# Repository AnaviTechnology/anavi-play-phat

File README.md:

# Anavi Play pHAT

Anavi Play pHAT is a simple open source hardware keyboard for Raspberry Pi pHAT (add-on board). Furthermore it supports reading data from various I2S sensor modules. It features:

* Eight buttons
* Slots for up to 3 plug and play I2C sensors for temperature, barometric pressure, humidity and light
* EEPROM

# License

The project is released under the [Creative Commons Attribution-ShareAlike 4.0 International (CC BY-SA 4.0)](https://creativecommons.org/licenses/by-sa/4.0/).

Note: This is a human-readable summary of (and not a substitute for) the [license](https://creativecommons.org/licenses/by-sa/4.0/legalcode).

You are free to:

Share — copy and redistribute the material in any medium or format Adapt — remix, transform, and build upon the material for any purpose, even commercially. The licensor cannot revoke these freedoms as long as you follow the license terms. Under the following terms:

Attribution — You must give appropriate credit, provide a link to the license, and indicate if changes were made. You may do so in any reasonable manner, but not in any way that suggests the licensor endorses you or your use. ShareAlike — If you remix, transform, or build upon the material, you must distribute your contributions under the same license as the original. No additional restrictions — You may not apply legal terms or technological measures that legally restrict others from doing anything the license permits. Notices:

You do not have to comply with the license for elements of the material in the public domain or where your use is permitted by an applicable exception or limitation. No warranties are given. The license may not give you all of the permissions necessary for your intended use. For example, other rights such as publicity, privacy, or moral rights may limit how you use the material.

You will have to provide a link to the original creator of the project http://www.anavi.technology on any documentation or website.

Credit can be attributed through a link to the creator website: http://www.anavi.technology

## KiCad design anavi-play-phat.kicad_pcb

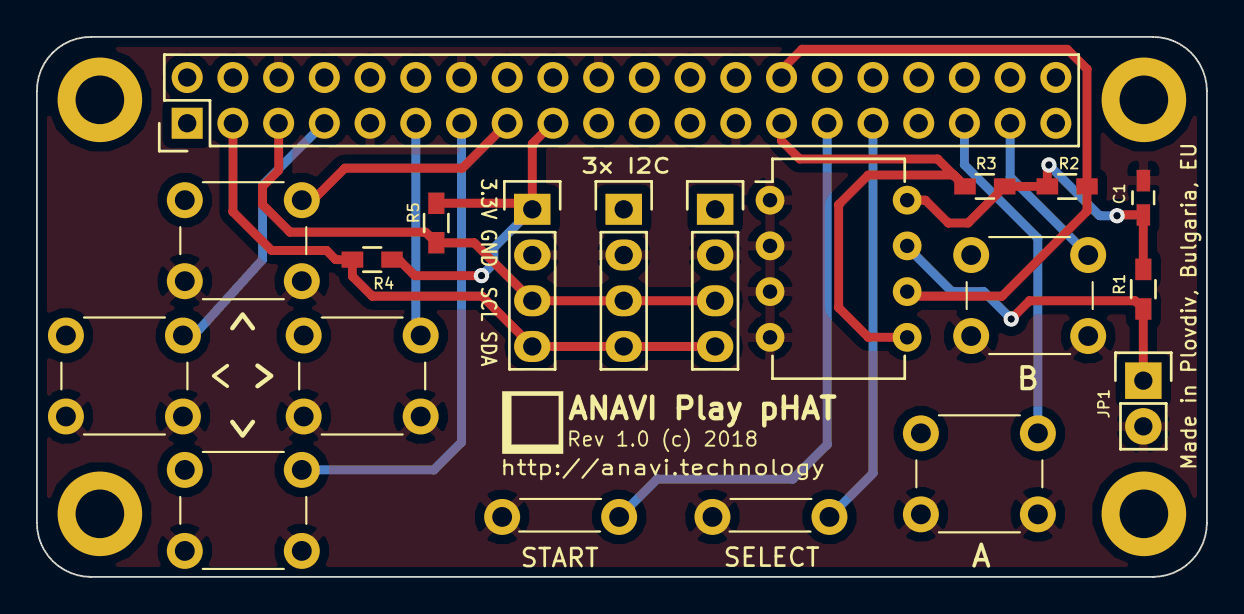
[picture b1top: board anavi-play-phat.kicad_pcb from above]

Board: 2 copper layers, 65.0 x 30.0 mm, 24 parts (0 on the bottom side), 16 nets.

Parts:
<: SW_DIP_x01; SW_PUSH_6mm_h4.3mm
<#2: SW_DIP_x01; SW_PUSH_6mm_h4.3mm
>: SW_DIP_x01; SW_PUSH_6mm_h4.3mm
>#2: SW_DIP_x01; SW_PUSH_6mm_h4.3mm
A: SW_DIP_x01; SW_PUSH_6mm_h4.3mm
B: SW_DIP_x01; SW_PUSH_6mm_h4.3mm
C1: 0.1; C_0603_HandSoldering
JP1: JUMPER; Pin_Header_Straight_1x02
R1: 1K; R_0603_HandSoldering
R2, R3, R4, R5: 4.7K; R_0603_HandSoldering
RASP_CONN1: Raspberry_PI; Pin_Header_Straight_2x20
REF1, REF2, REF3, REF4: MountingHole_2.7mm_M2.5_DIN965_Pad
SELECT: SW_DIP_x01; SW_PUSH_6mm_h4.3mm
SENS1, SENS2, SENS3: I2C_SENS_1; Pin_Header_Straight_1x04
START: SW_DIP_x01; SW_PUSH_6mm_h4.3mm
U1: CAT24C32WI-GT3; DIP-8_W7.62mm

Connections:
+3V3: C1.1, R1.1, R2.1, R3.1, R4.1, R5.1, RASP_CONN1.1, RASP_CONN1.17, SENS1.1, SENS2.1, SENS3.1, U1.8
+5V: RASP_CONN1.2, RASP_CONN1.4
GND: <.2, <#2.2, >.2, >#2.2, A.2, B.2, C1.2, JP1.2, RASP_CONN1.6, RASP_CONN1.9, RASP_CONN1.14, RASP_CONN1.20, RASP_CONN1.25, RASP_CONN1.30, RASP_CONN1.34, RASP_CONN1.39, SELECT.2, SENS1.2, SENS2.2, SENS3.2, START.2, U1.1, U1.2, U1.3, U1.4
unnamed: JP1.1, R1.2, U1.7
unnamed: R2.2, RASP_CONN1.28, U1.6
unnamed: R3.2, RASP_CONN1.27, U1.5
unnamed: R4.2, RASP_CONN1.3, SENS1.4, SENS2.4, SENS3.4
unnamed: R5.2, RASP_CONN1.5, SENS1.3, SENS2.3, SENS3.3
unnamed: <.1, RASP_CONN1.7
unnamed: >.1, RASP_CONN1.11
unnamed: <#2.1, RASP_CONN1.13
unnamed: >#2.1, RASP_CONN1.15
unnamed: RASP_CONN1.29, START.1
unnamed: RASP_CONN1.31, SELECT.1
unnamed: A.1, RASP_CONN1.35
unnamed: B.1, RASP_CONN1.37

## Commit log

2018-06-24 anavi-play-phat.kicad_pcb: Update arrows
2018-06-25 anavi-play-phat.kicad_pcb: Update silkscreen
2018-06-25 anavi-play-phat.kicad_pcb: Adjust buttons
2018-07-30 Migrate to KiCad 5.0.0-fee4fd1
    Tested on Ubuntu 18.04

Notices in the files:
anavi-play-phat.kicad_pcb:
Rev 1.0 (c) 2018
